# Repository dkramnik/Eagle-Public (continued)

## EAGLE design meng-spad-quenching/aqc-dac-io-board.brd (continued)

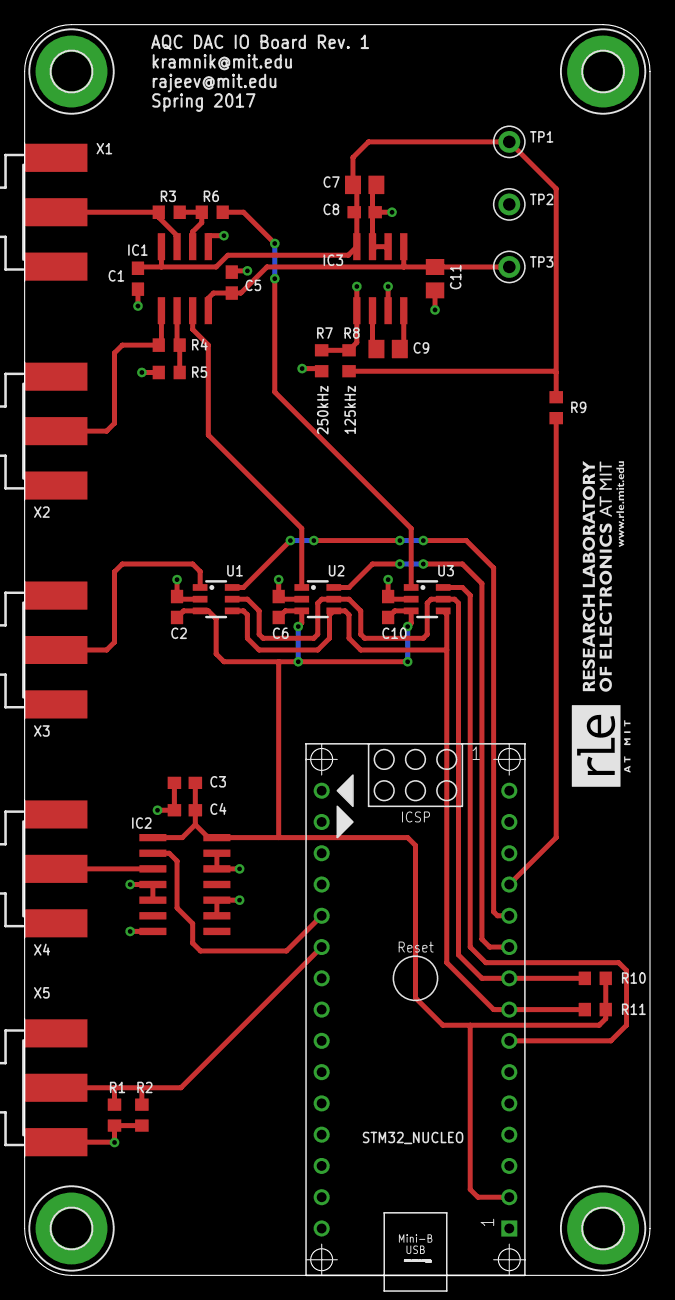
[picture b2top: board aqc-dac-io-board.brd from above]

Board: 2 copper layers, 50.8 x 101.6 mm, 41 parts (0 on the bottom side), 23 nets.

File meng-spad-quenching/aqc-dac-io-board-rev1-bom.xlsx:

| aqc-dac-io-board-rev1 BOM
 | Note: Cost is with MIT negotiated price, bulk discount not included.
BOM # | Part | Value | Rating | Package | Description | Digikey P/N | Cost/Unit | Qty. | Cost/Qty. | Comment
1 | C1, C2, C3, C5, C6, C8, C10 | 100n | 16V | C0603 |  |  |  | 7 | 0 | Generic
2 | C4 | 10n | 16V | C0603 |  |  |  | 1 | 0 | Generic
3 | C7, C9, C11 | 4u7 | 16V | C0805 |  |  |  | 3 | 0
4 | IC1 | LT1366 |  | SO08 | IC OPAMP GP 400KHZ RRO 8SO | LT1366CS8#PBF-ND | 7.34 | 1 | 7.34
5 | IC2 | 74LVT126 |  | SO14 | IC BUFF TRI-ST QD N-INV 14SOIC | 1727-6116-ND | 0.43 | 1 | 0.43
6 | IC3 | MAX1680 |  | SO8 | IC REG SWITCHD CAP INV 8SOIC | MAX1680ESA+-ND | 5.13 | 1 | 5.13
7 | R1, R2 | 100R | 1/8W | R0603 |  |  |  | 2 | 0
8 | R3 | 15k0 | 1/8W, 1% | R0603 |  |  |  | 1 | 0
9 | R4 | 5k11 | 1/8W, 1% | R0603 |  |  |  | 1 | 0
10 | R5, R6 | 10k0 | 1/8W, 1% | R0603 |  |  |  | 2 | 0
11 | R7, R9 | 0R | 1/8W | R0603 |  |  |  | 2 | 0 | Generic
12 | R8 | DNP |  | R0603 |  |  |  | 1 | 0 | Generic
13 | R10 | 2k2 | 1/8W | R0603 |  |  |  | 1 | 0
14 | R11 | 2k2 | 1/8W | R0603 |  |  |  | 1 | 0
15 | TP1 | Red TP PP_P5V0 |  |  |  |  |  | 1 | 0
16 | TP2 | Black TP GND |  |  |  |  |  | 1 | 0
17 | TP3 | Blue TP PP_N5V0 |  |  |  |  |  | 1 | 0
18 | U1, U2, U3 | MCP4725 |  | SOT23-6 |  |  |  | 3 | 0
19 | X1, X2, X3, X4, X5 | SMA SMT |  | SMA SMT |  |  |  | 5 | 0
20 | STM32 | Nucleo MCU |  | ARDUINO_NANO |  |  |  | 1 | 0
21 | STM32 | 1x15 Female Header |  | ARDUINO_NANO |  |  |  | 2 | 0
 |  |  |  |  |  |  | Total: |  | 12.899999999999999

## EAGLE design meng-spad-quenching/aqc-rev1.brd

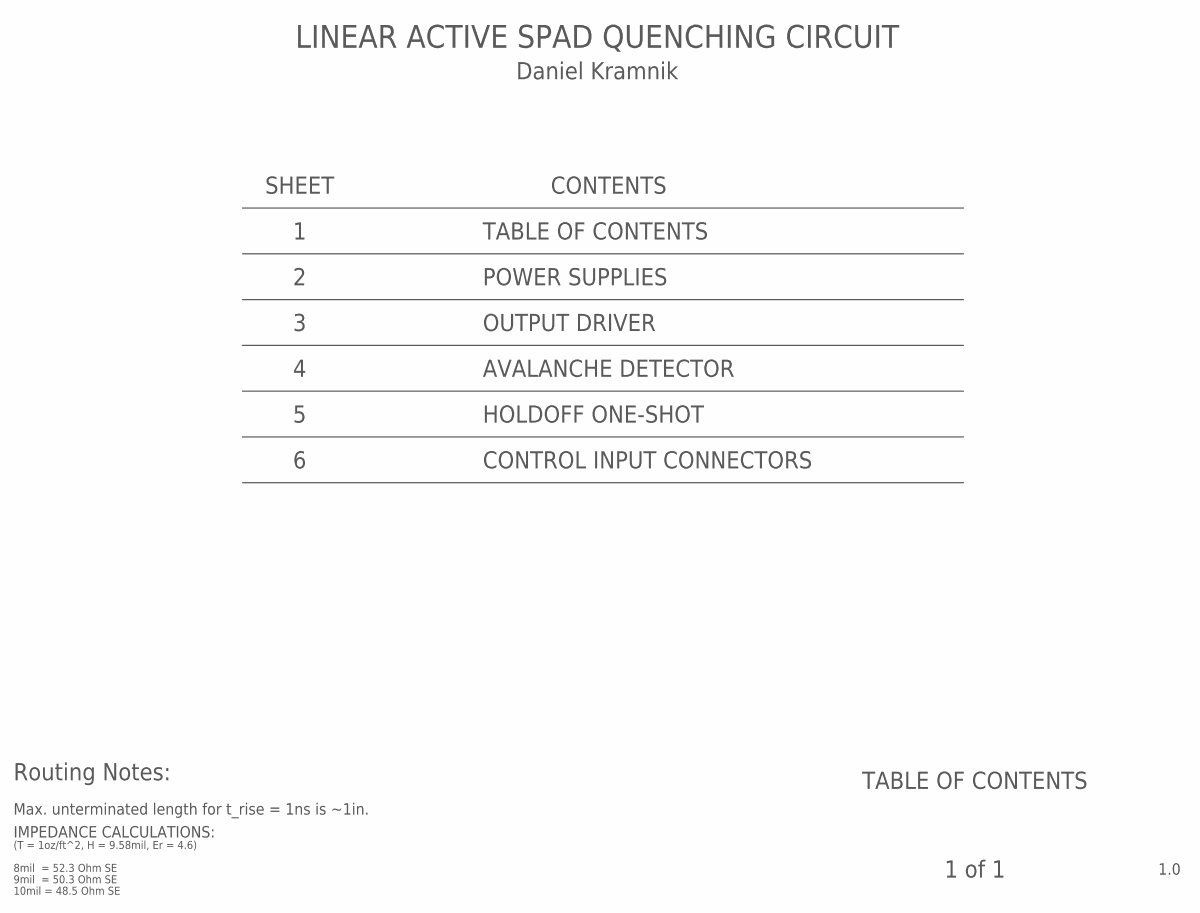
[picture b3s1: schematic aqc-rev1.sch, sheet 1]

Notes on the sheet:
IMPEDANCE CALCULATIONS:
(T = 1oz/ft^2, H = 9.58mil, Er = 4.6)
9mil = 50.3 Ohm SE
10mil = 48.5 Ohm SE
8mil = 52.3 Ohm SE
TABLE OF CONTENTS
1.0
1 of 1
LINEAR ACTIVE SPAD QUENCHING CIRCUIT
SHEET
CONTENTS
Daniel Kramnik
POWER SUPPLIES
OUTPUT DRIVER
AVALANCHE DETECTOR
HOLDOFF ONE-SHOT
CONTROL INPUT CONNECTORS
Routing Notes:
Max. unterminated length for t_rise = 1ns is ~1in.

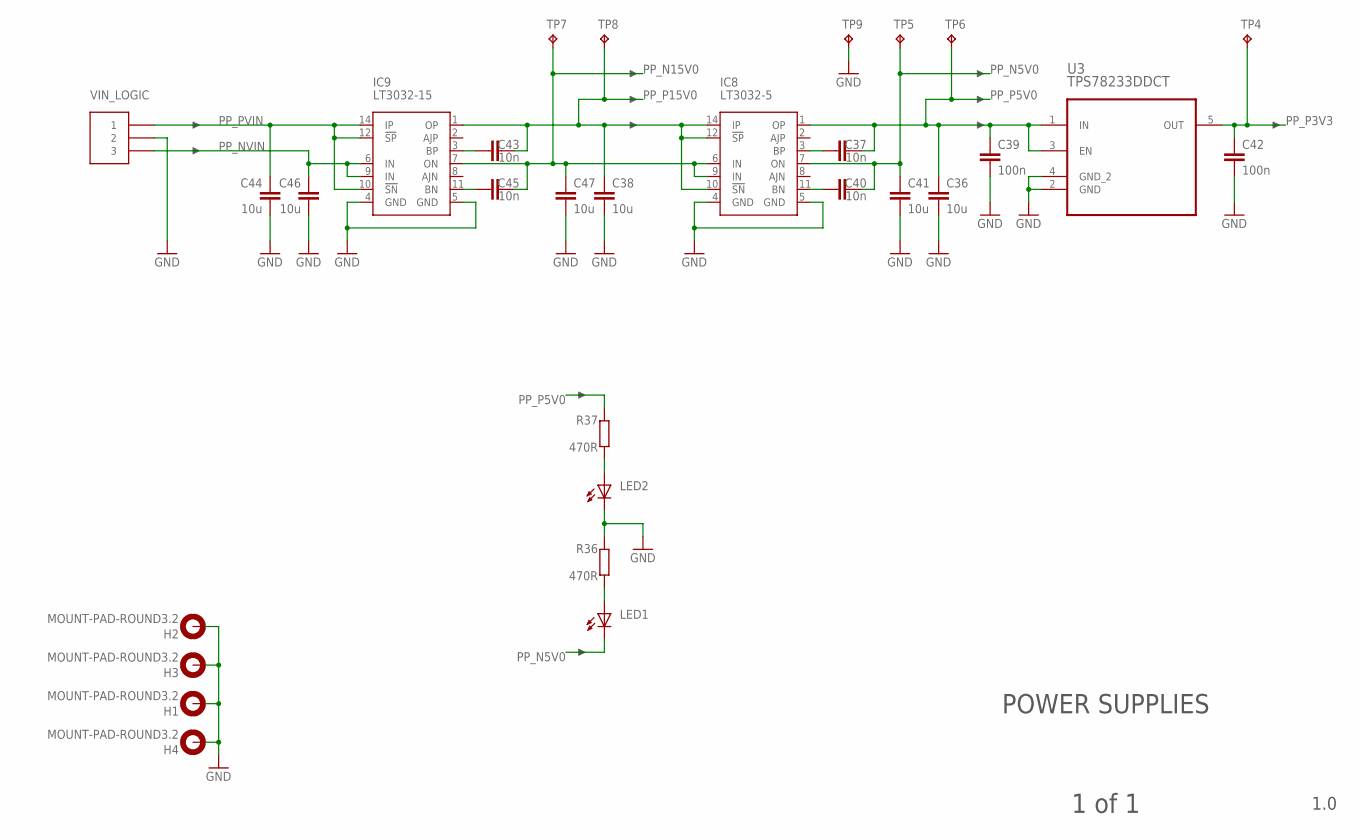
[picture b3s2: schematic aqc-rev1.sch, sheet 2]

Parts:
C36, C38, C41, C44, C46, C47: 10u; C1206
C37, C40, C43, C45: 10n; C0603
C39, C42: 100n; C0603
H1, H2, H3, H4: MOUNT-PAD-ROUND3.2; 3,2-PAD
IC8: LT3032-5; DFN14-4X3DE
IC9: LT3032-15; DFN14-4X3DE
J1: VIN_LOGIC; CONN_MOLEX_3PIN_MINI-FIT_JR
LED1, LED2: LEDCHIP-LED0805; CHIP-LED0805
R36, R37: 470R; R0805
TP4, TP5, TP6, TP7, TP8, TP9: TPTP20R; TP20R
U3: TPS78233DDCT; SOT95P280X110-5N

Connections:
GND: C36.2, C38.2, C39.2, C41.2, C42.2, C44.2, C46.2, C47.2, H1.B3,2, H2.B3,2, H3.B3,2, H4.B3,2, IC8.4 (GND), IC8.5 (GND), IC9.4 (GND), IC9.5 (GND), J1.2, LED2.C, R36.2, TP9.TP, U3.2 (GND), U3.4 (GND_2); also elsewhere on the board
unnamed: C37.1, IC8.3 (BP)
unnamed: C40.1, IC8.11 (BN)
unnamed: C43.1, IC9.3 (BP)
unnamed: C45.1, IC9.11 (BN)
unnamed: LED1.A, R36.1
unnamed: LED2.A, R37.1
PP_N5V0: C40.2, C41.1, IC8.7 (ON), LED1.C, TP5.TP; also elsewhere on the board
PP_N15V0: C45.2, C47.1, IC8.6 (IN), IC8.9 (IN), IC9.7 (ON), TP7.TP
PP_NVIN: C46.1, IC9.6 (IN), IC9.9 (IN), J1.3
PP_P3V3: C42.1, TP4.TP, U3.5 (OUT); also elsewhere on the board
PP_P5V0: C36.1, C37.2, C39.1, IC8.1 (OP), R37.2, TP6.TP, U3.1 (IN), U3.3 (EN); also elsewhere on the board
PP_P15V0: C38.1, C43.2, IC8.10 (!SN), IC8.12 (!SP), IC8.14 (IP), IC9.1 (OP), TP8.TP; also elsewhere on the board
PP_PVIN: C44.1, IC9.10 (!SN), IC9.12 (!SP), IC9.14 (IP), J1.1

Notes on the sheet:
POWER SUPPLIES
1.0
1 of 1

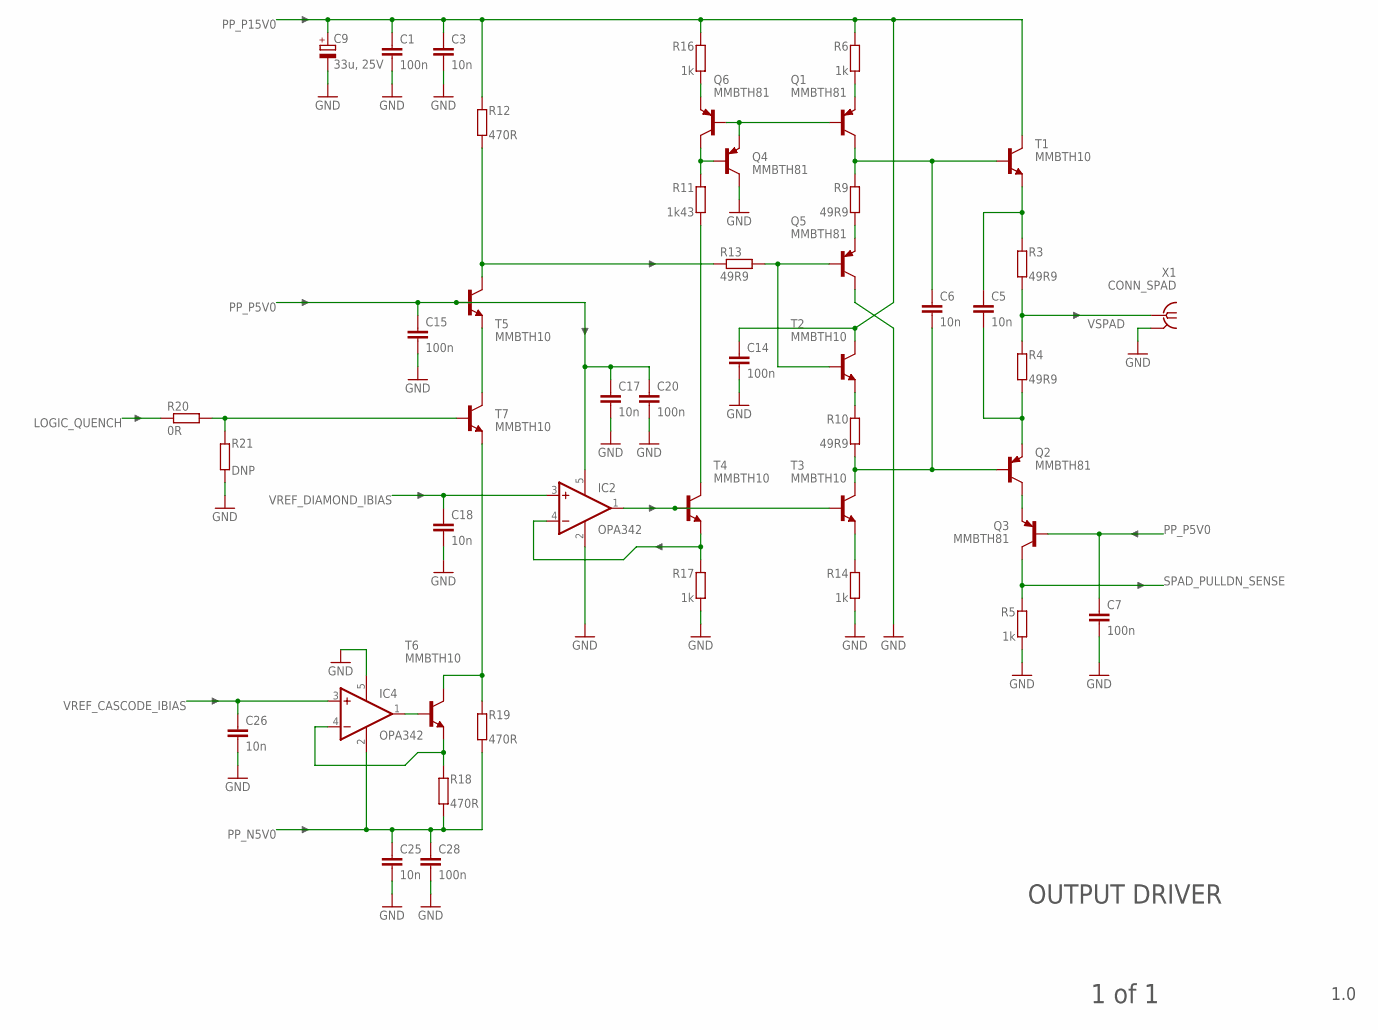
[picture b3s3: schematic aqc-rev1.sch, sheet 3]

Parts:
C1, C7, C14, C15: 100n; C0603
C3, C5, C6: 10n; C0603
C9: 33u, 25V; CT7343
C17, C18, C25, C26: 10n; C0402
C20, C28: 100n; C0402
IC2, IC4: OPA342; SOT23-5
Q1, Q2, Q3, Q4, Q5, Q6: MMBTH81; SOT23-BEC
R3, R4, R9, R10, R13: 49R9; R0603
R5, R6, R14, R16, R17: 1k; R0603
R11: 1k43; R0603
R12, R18, R19: 470R; R0603
R20: 0R; R0603
R21: DNP; R0603
T1, T2, T3, T4, T5, T6, T7: MMBTH10; SOT23-BEC
X1: CONN_SPAD; J502-ND-142-0711-871/876

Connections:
GND: C1.2, C3.2, C7.2, C9.-, C14.2, C15.2, C17.2, C18.2, C20.2, C25.2, C26.2, C28.2, IC2.2 (V-), IC4.5 (V+), Q4.C, Q5.C, R5.1, R14.1, R17.1, R21.2, X1.G@1 (GND), X1.G@2 (GND), X1.G@3 (GND), X1.G@4 (GND); also elsewhere on the board
LOGIC_QUENCH: R20.2; also elsewhere on the board
LOGIC_QUENCH_ATTEN: R20.1, R21.1, T7.B
unnamed: C5.1, R3.2, T1.E
unnamed: Q2.C, Q3.E
unnamed: Q5.E, R9.1
unnamed: C6.1, Q1.C, R9.2, T1.B
unnamed: R10.2, T2.E
unnamed: C5.2, Q2.E, R4.1
unnamed: T5.E, T7.C
unnamed: IC2.1 (OUT), T3.B, T4.B
unnamed: Q4.B, Q6.C, R11.2
unnamed: C6.2, Q2.B, R10.1, T3.C
unnamed: R14.2, T3.E
unnamed: Q5.B, R13.1, T2.B
unnamed: R12.1, R13.2, T5.C
unnamed: IC2.4 (-IN), R17.2, T4.E
unnamed: R19.2, T6.C, T7.E
unnamed: Q1.E, R6.1
unnamed: R11.1, T4.C
unnamed: Q6.E, R16.1
unnamed: IC4.1 (OUT), T6.B
unnamed: Q1.B, Q4.E, Q6.B
unnamed: IC4.4 (-IN), R18.2, T6.E
PP_N5V0: C25.1, C28.1, IC4.2 (V-), R18.1, R19.1; also elsewhere on the board
PP_P5V0: C7.1, C15.1, C17.1, C20.1, IC2.5 (V+), Q3.B, T5.B; also elsewhere on the board
PP_P15V0: C1.1, C3.1, C9.+, C14.1, R6.2, R12.2, R16.2, T1.C, T2.C; also elsewhere on the board
SPAD_PULLDN_SENSE: Q3.C, R5.2; also elsewhere on the board
VREF_CASCODE_IBIAS: C26.1, IC4.3 (+IN); also elsewhere on the board
VREF_DIAMOND_IBIAS: C18.1, IC2.3 (+IN); also elsewhere on the board
VSPAD: R3.1, R4.2, X1.1

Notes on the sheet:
OUTPUT DRIVER
1.0
1 of 1

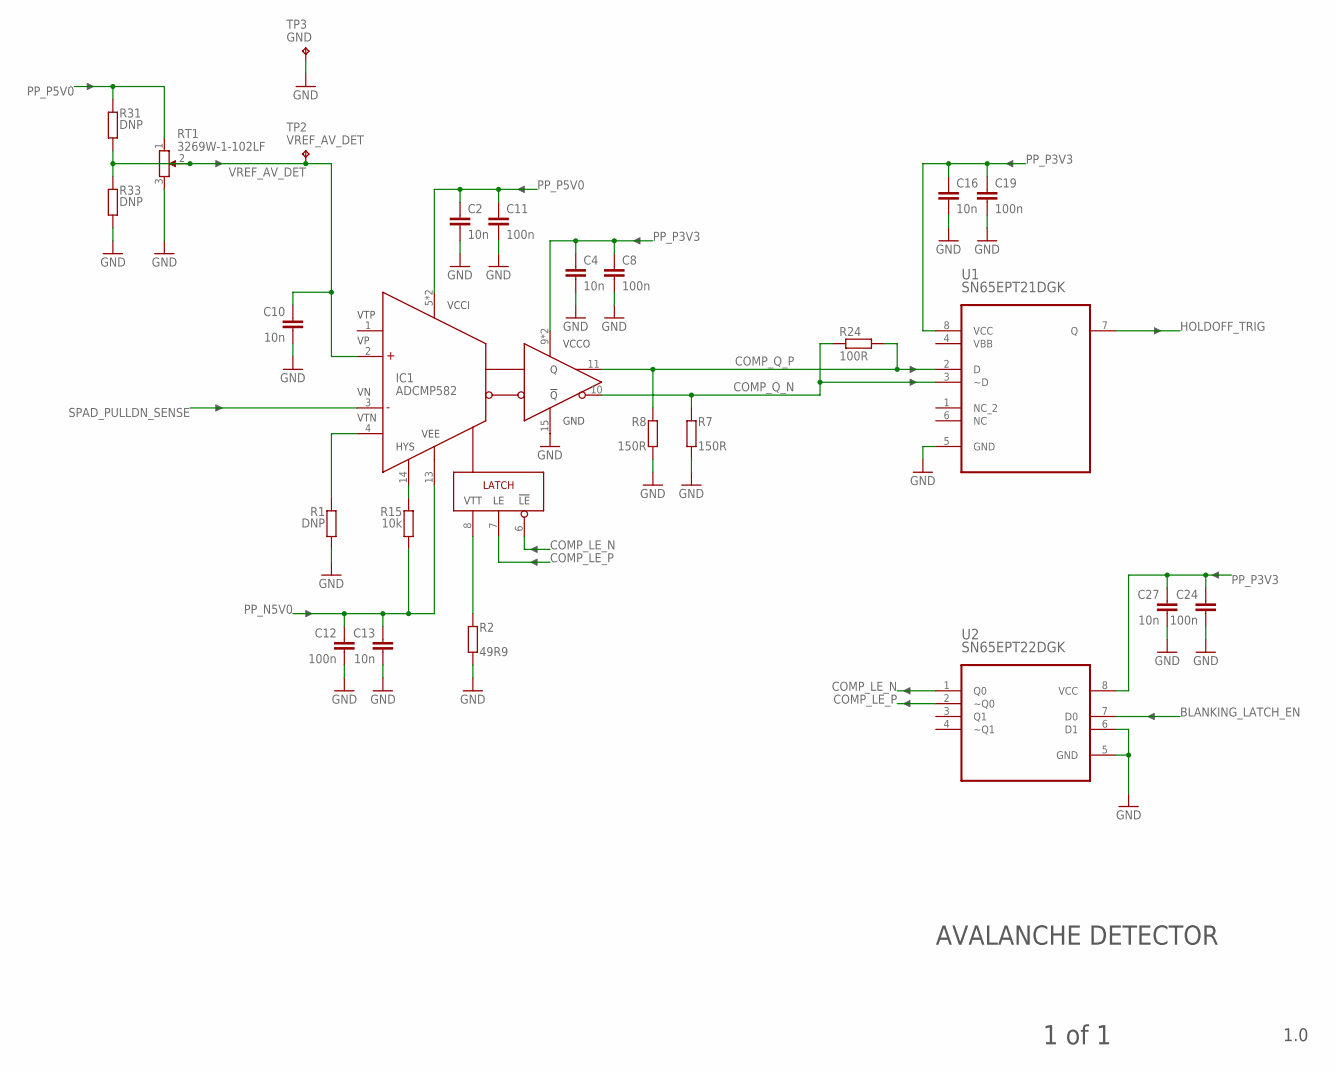
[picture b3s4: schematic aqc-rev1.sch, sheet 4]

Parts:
C2, C4, C13, C16, C27: 10n; C0402
C8, C11, C12, C19, C24: 100n; C0402
C10: 10n; C0603
IC1: ADCMP582; QFN50P300X300X80-16N
R1, R31, R33: DNP; R0603
R2: 49R9; R0603
R7, R8: 150R; R0402
R15: 10k; R0603
R24: 100R; R0402
RT1: 3269W-1-102LF; 3269W
TP2: VREF_AV_DET; KEYSTONE_5000_MINIATURE
TP3: GND; KEYSTONE_5000_MINIATURE
U1: SN65EPT21DGK; SOP65P490X110-8N
U2: SN65EPT22DGK; SOP65P490X110-8N

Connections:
BLANKING_LATCH_EN: U2.7 (D0); also elsewhere on the board
COMP_LE_N: IC1.6 (!LE), U2.1 (Q0)
COMP_LE_P: IC1.7 (LE), U2.2 (~Q0)
COMP_Q_N: IC1.10 (!Q), R7.1, R24.1, U1.3 (~D)
COMP_Q_P: IC1.11 (Q), R8.1, R24.2, U1.2 (D)
GND: C2.2, C4.2, C8.2, C10.2, C11.2, C12.2, C13.2, C16.2, C19.2, C24.2, C27.2, IC1.15 (GND), R1.1, R2.2, R7.2, R8.2, R33.1, RT1.3, TP3.P$1, U1.5 (GND), U2.5 (GND), U2.6 (D1); also elsewhere on the board
HOLDOFF_TRIG: U1.7 (Q); also elsewhere on the board
unnamed: IC1.4 (VTN), R1.2
unnamed: IC1.14 (HYS), R15.2
unnamed: IC1.8 (VTT), R2.1
PP_N5V0: C12.1, C13.1, IC1.13 (VEE), R15.1; also elsewhere on the board
PP_P3V3: C4.1, C8.1, C16.1, C19.1, C24.1, C27.1, IC1.9 (VCCO), IC1.12 (VCCO), U1.8 (VCC), U2.8 (VCC); also elsewhere on the board
PP_P5V0: C2.1, C11.1, IC1.5 (VCCI), IC1.16 (VCCI), R31.2, RT1.1; also elsewhere on the board
SPAD_PULLDN_SENSE: IC1.3 (VN); also elsewhere on the board
VBB: U1.4 (VBB)
VREF_AV_DET: C10.1, IC1.2 (VP), R31.1, R33.2, RT1.2, TP2.P$1

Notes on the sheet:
AVALANCHE DETECTOR
1.0
1 of 1

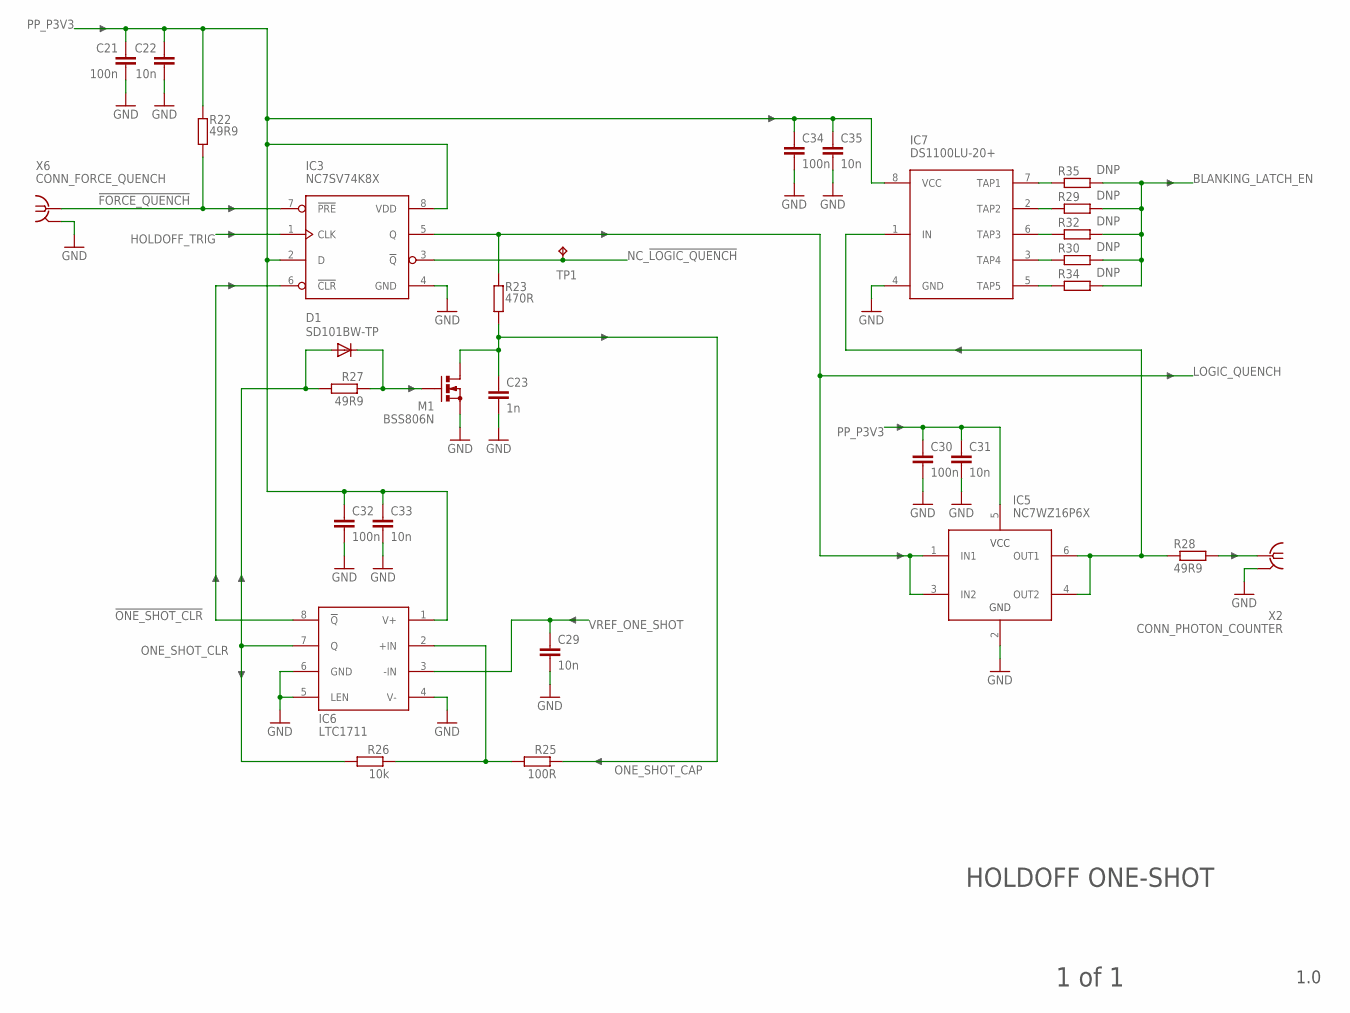
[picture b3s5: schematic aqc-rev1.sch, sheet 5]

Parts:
C21, C30, C32, C34: 100n; C0402
C22, C29, C31, C33, C35: 10n; C0402
C23: 1n; C0603
D1: SD101BW-TP; SOD123
IC3: NC7SV74K8X; US8_3.1MM_JDEC_MO-187
IC5: NC7WZ16P6X; SC70-6L
IC6: LTC1711; MSOP8
IC7: DS1100LU-20+; MSOP8
M1: BSS806N; SOT23R_INFINEON
R22, R27, R28: 49R9; R0603
R23: 470R; R0603
R25: 100R; R0603
R26: 10k; R0603
R29, R30, R32, R34, R35: DNP; R0603
TP1: TPTP08R; TP08R
X2: CONN_PHOTON_COUNTER; J502-ND-142-0711-871/876
X6: CONN_FORCE_QUENCH; J502-ND-142-0711-871/876; MPN 142-0711-871

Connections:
!FORCE_QUENCH: IC3.7 (!PRE), R22.1, X6.1
!ONE_SHOT_CLR: IC3.6 (!CLR), IC6.8 (!Q)
BLANKING_LATCH_EN: R29.1, R30.1, R32.1, R34.1, R35.1; also elsewhere on the board
GND: C21.2, C22.2, C23.2, C29.2, C30.2, C31.2, C32.2, C33.2, C34.2, C35.2, IC3.4 (GND), IC5.2 (GND), IC6.4 (V-), IC6.5 (LEN), IC6.6 (GND), IC7.4 (GND), M1.2 (S), X2.G@1 (GND), X2.G@2 (GND), X2.G@3 (GND), X2.G@4 (GND), X6.G@1 (GND), X6.G@2 (GND), X6.G@3 (GND), X6.G@4 (GND); also elsewhere on the board
HOLDOFF_TRIG: IC3.1 (CLK); also elsewhere on the board
LOGIC_QUENCH: IC3.5 (Q), IC5.1 (IN1), IC5.3 (IN2), R23.2; also elsewhere on the board
unnamed: R28.1, X2.1
unnamed: IC6.2 (+IN), R25.1, R26.2
unnamed: D1.C, M1.1 (G), R27.2
unnamed: IC5.4 (OUT2), IC5.6 (OUT1), IC7.1 (IN), R28.2
NC_!LOGIC_QUENCH: IC3.3 (!Q), TP1.TP
ONE_SHOT_CAP: C23.1, M1.3 (D), R23.1, R25.2
ONE_SHOT_CLR: D1.A, IC6.7 (Q), R26.1, R27.1
PP_P3V3: C21.1, C22.1, C30.1, C31.1, C32.1, C33.1, C34.1, C35.1, IC3.2 (D), IC3.8 (VDD), IC5.5 (VCC), IC6.1 (V+), IC7.8 (VCC), R22.2; also elsewhere on the board
TAP1: IC7.7 (TAP1), R35.2
TAP2: IC7.2 (TAP2), R29.2
TAP3: IC7.6 (TAP3), R32.2
TAP4: IC7.3 (TAP4), R30.2
TAP5: IC7.5 (TAP5), R34.2
VREF_ONE_SHOT: C29.1, IC6.3 (-IN); also elsewhere on the board

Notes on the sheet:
HOLDOFF ONE-SHOT
1.0
1 of 1

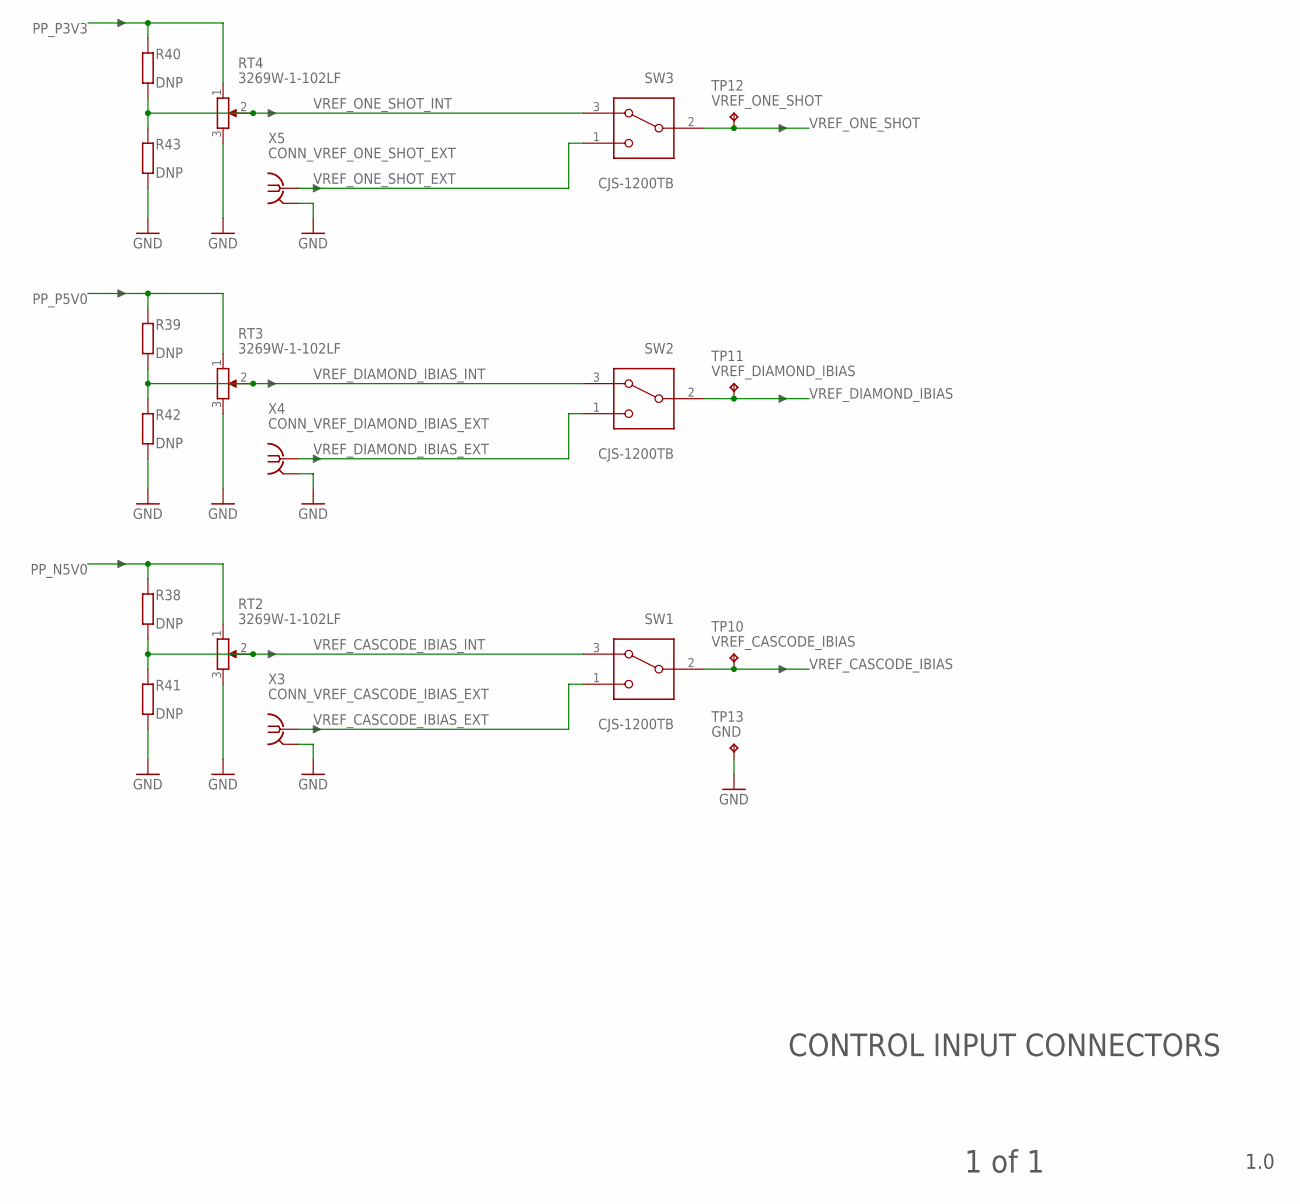
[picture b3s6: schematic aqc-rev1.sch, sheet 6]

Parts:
R38, R39, R40, R41, R42, R43: DNP; R0603
RT2, RT3, RT4: 3269W-1-102LF; 3269W
SW1, SW2, SW3: CJS-1200TB
TP10: VREF_CASCODE_IBIAS; KEYSTONE_5000_MINIATURE
TP11: VREF_DIAMOND_IBIAS; KEYSTONE_5000_MINIATURE
TP12: VREF_ONE_SHOT; KEYSTONE_5000_MINIATURE
TP13: GND; KEYSTONE_5000_MINIATURE
X3: CONN_VREF_CASCODE_IBIAS_EXT; J502-ND-142-0711-871/876
X4: CONN_VREF_DIAMOND_IBIAS_EXT; J502-ND-142-0711-871/876
X5: CONN_VREF_ONE_SHOT_EXT; J502-ND-142-0711-871/876

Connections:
GND: R41.2, R42.2, R43.2, RT2.3, RT3.3, RT4.3, TP13.P$1, X3.G@1 (GND), X3.G@2 (GND), X3.G@3 (GND), X3.G@4 (GND), X4.G@1 (GND), X4.G@2 (GND), X4.G@3 (GND), X4.G@4 (GND), X5.G@1 (GND), X5.G@2 (GND), X5.G@3 (GND), X5.G@4 (GND); also elsewhere on the board
PP_N5V0: R38.1, RT2.1; also elsewhere on the board
PP_P3V3: R40.1, RT4.1; also elsewhere on the board
PP_P5V0: R39.1, RT3.1; also elsewhere on the board
VREF_CASCODE_IBIAS: SW1.2 (COM), TP10.P$1; also elsewhere on the board
VREF_CASCODE_IBIAS_EXT: SW1.1 (NO), X3.1
VREF_CASCODE_IBIAS_INT: R38.2, R41.1, RT2.2, SW1.3 (NC)
VREF_DIAMOND_IBIAS: SW2.2 (COM), TP11.P$1; also elsewhere on the board
VREF_DIAMOND_IBIAS_EXT: SW2.1 (NO), X4.1
VREF_DIAMOND_IBIAS_INT: R39.2, R42.1, RT3.2, SW2.3 (NC)
VREF_ONE_SHOT: SW3.2 (COM), TP12.P$1; also elsewhere on the board
VREF_ONE_SHOT_EXT: SW3.1 (NO), X5.1
VREF_ONE_SHOT_INT: R40.2, R43.1, RT4.2, SW3.3 (NC)

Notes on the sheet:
CONTROL INPUT CONNECTORS
1.0
1 of 1

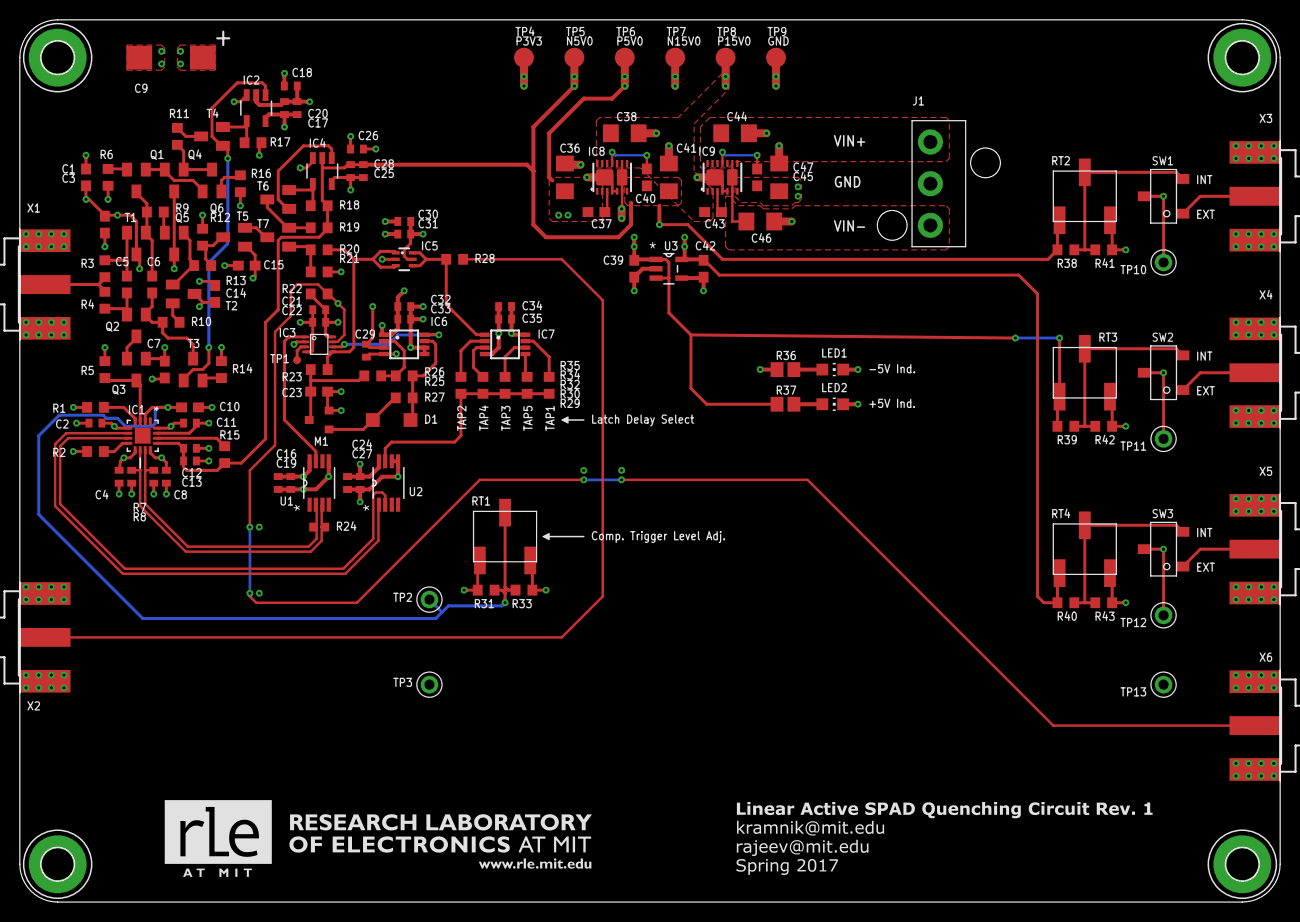
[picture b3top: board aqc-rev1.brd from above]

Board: 4 copper layers, 127.0 x 88.9 mm, 150 parts (0 on the bottom side), 72 nets.

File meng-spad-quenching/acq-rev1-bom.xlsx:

aqc-rev1 BOM
Note: Cost is with MIT negotiated price.
Part | Value | Rating | Package | Description | Digikey P/N | Cost/Unit | Qty. | Cost/Qty.
C1, C7, C14, C15, C39, C42 | 100n |  | C0603 | CAP CER 0.1UF 25V X7R 0603 | 490-1524-1-ND | 0.09 | 6 | 0.54
C2, C4, C13, C16, C17, C18, C22, C25, C26, C27, C29, C31, C33, C35 | 10n |  | C0402 | CAP CER 10000PF 25V X7R 0402 | 490-1312-1-ND | 0.09 | 14 | 1.26
C3, C5, C6, C10, C37, C40, C43, C45 | 10n |  | C0603 | CAP CER 10000PF 25V X7R 0603 | 1276-1132-1-ND | 0.09 | 8 | 0.72
C8, C11, C12, C19, C20, C21, C24, C28, C30, C32, C34 | 100n |  | C0402 | CAP CER 0.1UF 25V X7R 0402 | 490-10698-1-ND | 0.09 | 11 | 0.99
C9 | 33u |  | C7343 | CAP ALUM POLY 33UF 20% 25V SMD | P16819-1-ND | 1.45 | 1 | 1.45
C23 | 1n |  | C0603 | CAP FILM 1000PF 2% 16VDC 0603 | PCF1453CT-ND | 0.38 | 1 | 0.38
C36, C38, C41, C44, C46, C47 | 10u |  | C1206 | CAP CER 10UF 25V X7R 1206 | 490-6518-1-ND | 0.22 | 6 | 1.32
D1 | SD101BW-TP |  | SOD123 | DIODE SCHOTTKY 50V 15MA SOD123 | SD101BWTPMSCT-ND | 0.3 | 1 | 0.3
IC1 | ADCMP582 |  | 16LFCSP | IC COMPARATOR PECL UFAST 16LFCSP | ADCMP582BCPZ-WP | 15.89 | 1 | 15.89
IC2, IC4 | OPA342 |  | SOT23-5 | IC OPAMP GP 1MHZ RRO SOT23-5 | 296-41474-1-ND | 0.97 | 2 | 1.94
IC3 | NC7SV74K8X |  | US8 | IC D-TYPE POS TRG SNGL US8 | NC7SV74K8XCT-ND | 0.51 | 1 | 0.51
IC5 | NC7WZ16P6X |  | SC70-6L | IC BUFFER DL UHS N-INV SC70-6 | NC7WZ16P6XCT-ND | 0.34 | 1 | 0.34
IC6 | LTC1711 |  | MSOP8 | IC COMP R-RINOUT SINGLE 8-MSOP | LT1711CMS8#PBF-ND | 4.4000000000000004 | 1 | 4.4000000000000004
IC7 | DS1100LU-20+ |  | MSOP8 | IC DELAY LINE 5TAP 20NS 8UMAX | DS1100LU-20+-ND | 5.14 | 1 | 5.14
IC8 | LT3032-5 |  | 14DFN | IC REG LDO +-5V 0.15A 14DFN | LT3032EDE-5#PBF-ND | 4.7 | 1 | 4.7
IC9 | LT3032-15 |  | 14DFN | IC REG LDO +-15V 0.15A 14DFN | LT3032EDE-15#PBF-ND | 4.7 | 1 | 4.7
J1 | VIN_LOGIC |  | Custom | CONN HEADER 3POS SNGL VERT GOLD | WM7251-ND | 1.2 | 1 | 1.2
LED1, LED2 | LEDCHIP-LED0805 |  | LED0805 | LED GREEN CLEAR 0805 SMD | 732-4986-1-ND | 0.28999999999999998 | 2 | 0.57999999999999996
M1 | BSS806N |  | SOT23R | MOSFET N-CH 20V 2.3A SOT23 | BSS806N H6327CT-ND | 0.3 | 1 | 0.3
Q1, Q2, Q3, Q4, Q5, Q6 | MMBTH81 |  | SOT23-BEC | TRANSISTOR RF PNP SOT-23 | MMBTH81CT-ND | 0.19 | 6 | 1.1400000000000001
R1, R21, R29, R30, R31, R32, R33, R34, R35, R38, R39, R40, R41, R42, R43 | DNP |  | R0603 | DNP, Buy Extra 0R Jumpers | N/A | 0 | 15 | 0
R2, R3, R4, R9, R10, R13, R22, R27, R28 | 49R9 |  | R0603 | RES SMD 49.9 OHM 1% 1/8W 0603 | RNCP0603FTD49R9CT-ND | 0.09 | 9 | 0.80999999999999994
R5, R6, R14, R16, R17 | 1k |  | R0603 | RES SMD 1K OHM 1% 1/8W 0603 | RNCP0603FTD1K00CT-ND | 0.09 | 5 | 0.44999999999999996
R7, R8 | 150R |  | R0402 | RES SMD 150 OHM 1% 1/10W 0402 | P150LCT-ND | 0.09 | 2 | 0.18
R11 | 1k43 |  | R0603 | RES SMD 1.43K OHM 1% 1/10W 0603 | 311-1.43KHRCT-ND | 0.09 | 1 | 0.09
R12, R18, R19, R23 | 470R |  | R0603 | RES SMD 470 OHM 1% 1/10W 0603 | RMCF0603FT470RCT-ND | 0.09 | 4 | 0.36
R15, R26 | 10k |  | R0603 | RES SMD 10K OHM 1% 1/10W 0603 | RMCF0603FT10K0CT-ND | 0.09 | 2 | 0.18
R20 | 0R |  | R0603 | RES SMD 0.0OHM JUMPER 1/10W 0603 | 311-0.0GRCT-ND | 0.09 | 1 | 0.09
R24, R25 | 100R |  | R0402 | RES SMD 100 OHM 1% 1/10W 0402 | P100LCT-ND | 0.09 | 2 | 0.18
R36, R37 | 150R |  | R0805 | RES SMD 150 OHM 1% 1/8W 0805 | 311-150CRCT-ND | 0.09 | 2 | 0.18
RT1, RT2, RT3, RT4 | 3269W-1-102LF |  | 3269W | TRIMMER 1K OHM 0.25W SMD | 3269W-1-102LF-ND | 4.1100000000000003 | 4 | 16.440000000000001
SW1, SW2, SW3 | CJS-1200TB |  | CJS-1200TB | SWITCH SLIDE DIP SPDT 100MA 6V | 563-1022-1-ND | 0.73 | 3 | 2.19
T1, T2, T3, T4, T5, T6, T7 | MMBTH10 |  | SOT23-BEC | TRANS VHF/UHF NPN 25V SOT-23 | MMBTH10-4LT1GOSCT-ND | 0.23 | 7 | 1.61
TP2, TP10, TP11, TP12. TP13 | White TP VREF |  | Custom | TEST POINT PC MINI .040"D WHITE | 36-5002-ND | 0.32 | 5 | 1.6
TP3, TP13 | Black TP GND |  | Custom | TEST POINT PC MINI .040"D BLACK | 36-5001-ND | 0.32 | 2 | 0.64
U1 | SN65EPT21DGK |  | 8VSSOP | IC XLATR DIFF PECL/LVDS 8VSSOP | 296-27264-5-ND | 3.4 | 1 | 3.4
U2 | SN65EPT22DGK |  | 8VSSOP | BUFFER DUAL LVPECL 3.3V 8VSSOP | 296-24086-5-ND | 3.4 | 1 | 3.4
U3 | TPS78233DDCT |  | 5SOT | IC REG LDO 3.3V 0.15A 5SOT | 296-24120-1-ND | 0.74 | 1 | 0.74
X1, X2, X3, X4, X5, X6 | CONN SMA |  | SMA-SMT | CONN SMA JACK 50 OHM EDGE MNT | WM5534-ND | 2.84 | 6 | 17.04
 |  |  |  |  |  | TOTAL: |  | 97.380000000000024

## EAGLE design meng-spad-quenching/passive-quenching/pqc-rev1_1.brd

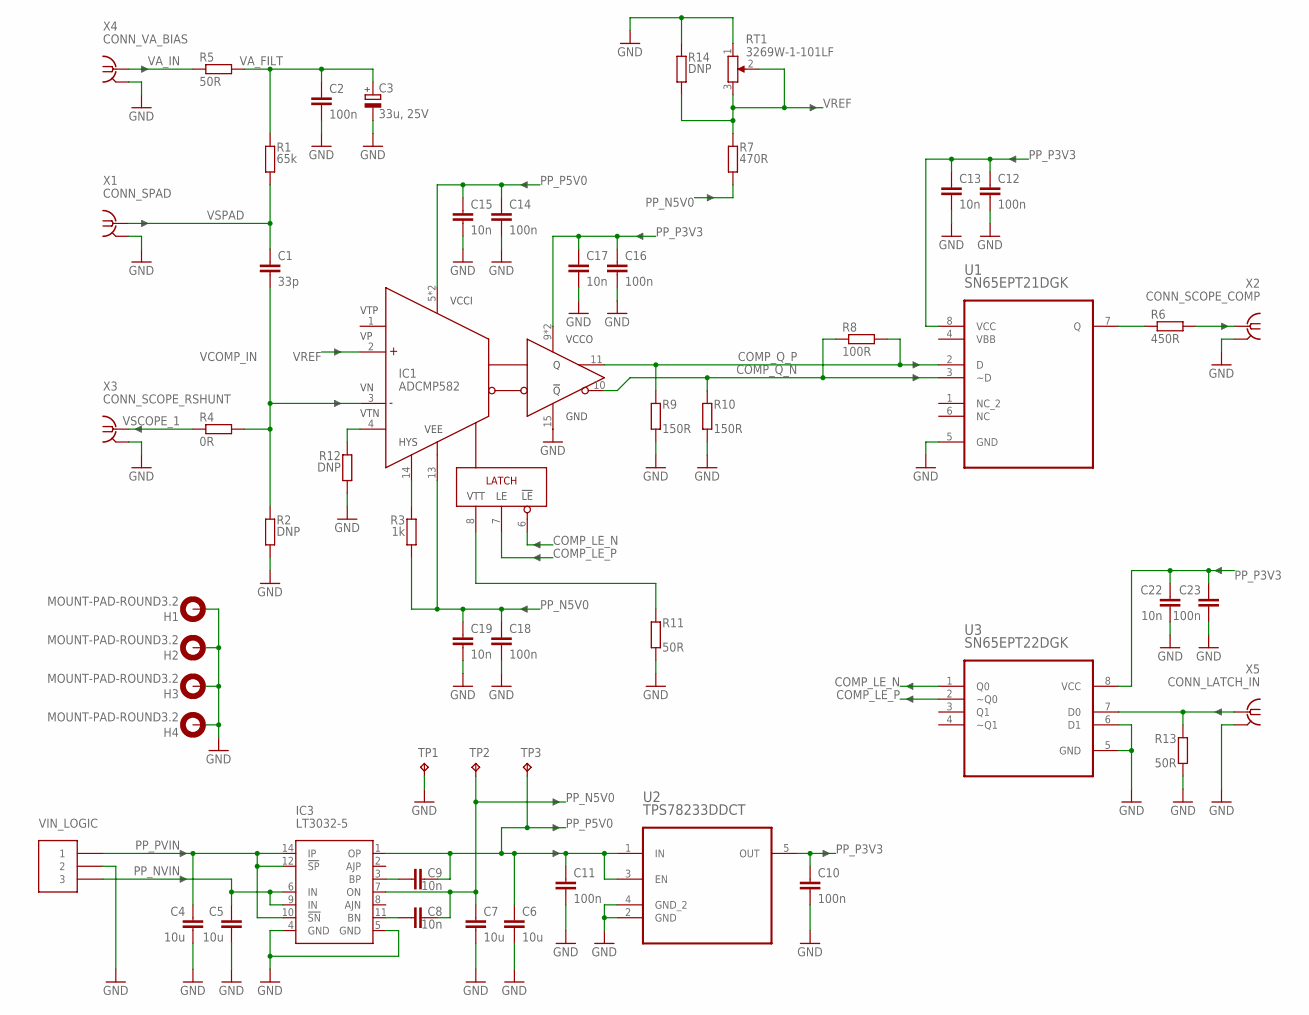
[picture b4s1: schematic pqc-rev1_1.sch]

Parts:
C1: 33p; C0805
C2: 100n; C0805
C3: 33u, 25V; CT7343
C4, C5, C6, C7: 10u; C1206
C8, C9, C13, C15, C17, C19, C22: 10n; C0603
C10, C11, C12, C14, C16, C18, C23: 100n; C0603
H1, H2, H3, H4: MOUNT-PAD-ROUND3.2; 3,2-PAD
IC1: ADCMP582; QFN50P300X300X80-16N
IC3: LT3032-5; DFN14-4X3DE
J1: VIN_LOGIC; CONN_MOLEX_3PIN_MINI-FIT_JR
R1: 65k; R0805
R2, R12: DNP; R0603
R3: 1k; R0805
R4: 0R; R0603
R5: 50R; R0805
R6: 450R; R0603
R7: 470R; R0805
R8: 100R; R0603
R9, R10: 150R; R0603
R11, R13: 50R; R0603
R14: DNP; R0805
RT1: 3269W-1-101LF; 3269W
TP1, TP2, TP3: TPTP20R; TP20R
U1: SN65EPT21DGK; SOP65P490X110-8N
U2: TPS78233DDCT; SOT95P280X110-5N
U3: SN65EPT22DGK; SOP65P490X110-8N
X1: CONN_SPAD; J502-ND-142-0711-871/876
X2: CONN_SCOPE_COMP; J502-ND-142-0711-871/876
X3: CONN_SCOPE_RSHUNT; J502-ND-142-0711-871/876
X4: CONN_VA_BIAS; J502-ND-142-0711-871/876
X5: CONN_LATCH_IN; J502-ND-142-0711-871/876; MPN 142-0711-871

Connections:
COMP_LE_N: IC1.6 (!LE), U3.1 (Q0)
COMP_LE_P: IC1.7 (LE), U3.2 (~Q0)
COMP_Q_N: IC1.10 (!Q), R8.1, R10.1, U1.3 (~D)
COMP_Q_P: IC1.11 (Q), R8.2, R9.1, U1.2 (D)
GND: C2.2, C3.-, C4.2, C5.2, C6.2, C7.2, C10.2, C11.2, C12.2, C13.2, C14.2, C15.2, C16.2, C17.2, C18.2, C19.2, C22.2, C23.2, H1.B3,2, H2.B3,2, H3.B3,2, H4.B3,2, IC1.15 (GND), IC3.4 (GND), IC3.5 (GND), J1.2, R2.1, R9.2, R10.2, R11.2, R12.1, R13.2, R14.2, RT1.1, TP1.TP, U1.5 (GND), U2.2 (GND), U2.4 (GND_2), U3.5 (GND), U3.6 (D1), X1.G@1 (GND), X1.G@2 (GND), X1.G@3 (GND), X1.G@4 (GND), X2.G@1 (GND), X2.G@2 (GND), X2.G@3 (GND), X2.G@4 (GND), X3.G@1 (GND), X3.G@2 (GND), X3.G@3 (GND), X3.G@4 (GND), X4.G@1 (GND), X4.G@2 (GND), X4.G@3 (GND), X4.G@4 (GND), X5.G@1 (GND), X5.G@2 (GND), X5.G@3 (GND), X5.G@4 (GND)
unnamed: R6.2, U1.7 (Q)
unnamed: R6.1, X2.1
unnamed: IC1.4 (VTN), R12.2
unnamed: IC1.14 (HYS), R3.2
unnamed: IC1.8 (VTT), R11.1
unnamed: C9.1, IC3.3 (BP)
unnamed: C8.1, IC3.11 (BN)
unnamed: R13.1, U3.7 (D0), X5.1
PP_N5V0: C7.1, C8.2, C18.1, C19.1, IC1.13 (VEE), IC3.7 (ON), R3.1, R7.1, TP2.TP
PP_NVIN: C5.1, IC3.6 (IN), IC3.9 (IN), J1.3
PP_P3V3: C10.1, C12.1, C13.1, C16.1, C17.1, C22.1, C23.1, IC1.9 (VCCO), IC1.12 (VCCO), U1.8 (VCC), U2.5 (OUT), U3.8 (VCC)
PP_P5V0: C6.1, C9.2, C11.1, C14.1, C15.1, IC1.5 (VCCI), IC1.16 (VCCI), IC3.1 (OP), TP3.TP, U2.1 (IN), U2.3 (EN)
PP_PVIN: C4.1, IC3.10 (!SN), IC3.12 (!SP), IC3.14 (IP), J1.1
VA_FILT: C2.1, C3.+, R1.2, R5.1
VA_IN: R5.2, X4.1
VBB: U1.4 (VBB)
VCOMP_IN: C1.2, IC1.3 (VN), R2.2, R4.1
VREF: IC1.2 (VP), R7.2, R14.1, RT1.2, RT1.3
VSCOPE_1: R4.2, X3.1
VSPAD: C1.1, R1.1, X1.1
